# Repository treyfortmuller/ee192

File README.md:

# EE192 Spring 2018: Team 6
Joey Kroeger, Trey Fortmuller, Charlene Shong

### Development Workflow
* The master branch should always be functional.
* For each checkoff, create a branch. When the branch is working and tested, merge it into master.

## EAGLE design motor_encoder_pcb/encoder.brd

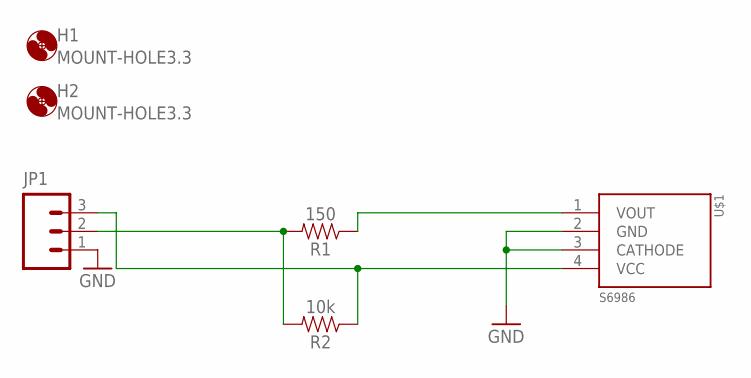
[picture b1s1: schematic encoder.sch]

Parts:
H1, H2: MOUNT-HOLE3.3; 3,3
JP1: M03PTH; 1X03
R1: 150; AXIAL-0.3
R2: 10k; AXIAL-0.3
U$1: S6986

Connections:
GND: JP1.1, U$1.2 (GND), U$1.3 (CATHODE)
unnamed: JP1.2, R1.P$2 (2), R2.P$2 (2)
unnamed: JP1.3, R2.P$1 (1), U$1.4 (VCC)
unnamed: R1.P$1 (1), U$1.1 (VOUT)

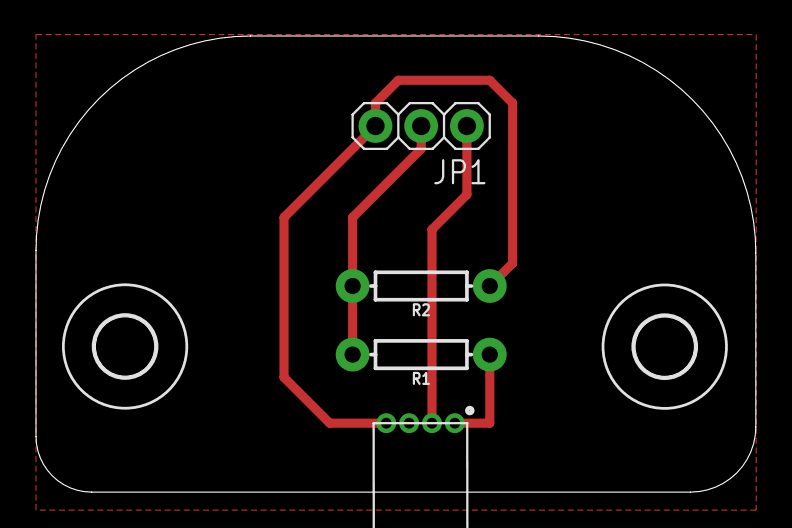
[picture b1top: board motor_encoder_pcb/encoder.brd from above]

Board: 2 copper layers, 40.0 x 25.3 mm, 6 parts (0 on the bottom side), 4 nets.

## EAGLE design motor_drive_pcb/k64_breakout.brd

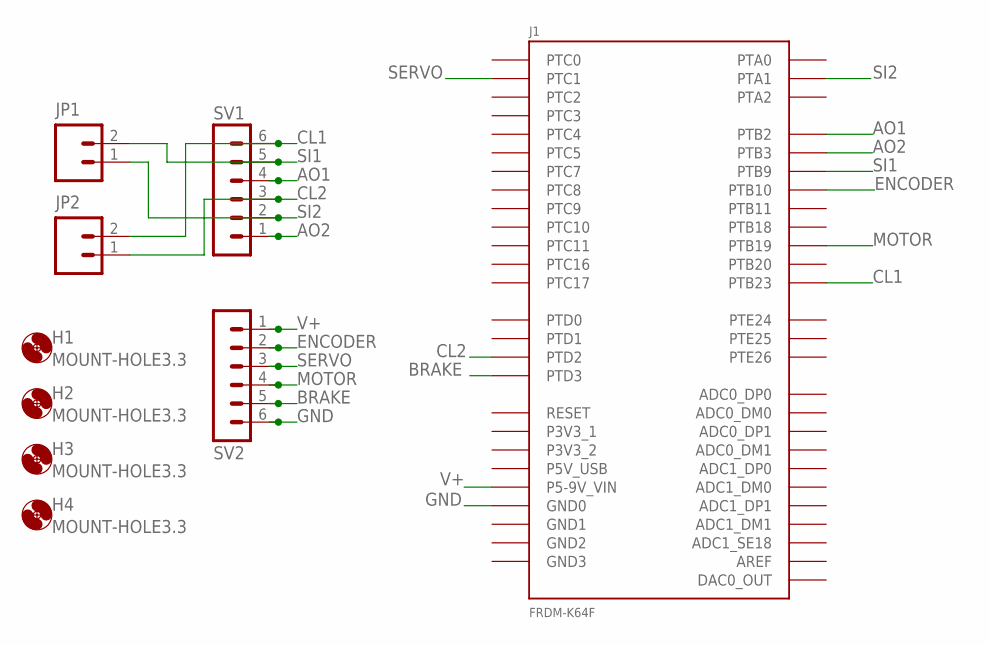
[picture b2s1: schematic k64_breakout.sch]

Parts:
H1, H2, H3, H4: MOUNT-HOLE3.3; 3,3
J1: FRDM-K64F
JP1, JP2: M02PTH; 1X02
SV1, SV2: MA06-1

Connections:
AO1: J1.J4-2 (PTB2), SV1.4
AO2: J1.J4-4 (PTB3), SV1.1
BRAKE: J1.J2-10 (PTD3), SV2.5
CL1: J1.J1-10 (PTB23), JP2.2, SV1.6
CL2: J1.J2-8 (PTD2), JP2.1, SV1.3
ENCODER: J1.J4-6 (PTB10), SV2.2
GND: J1.J2-3 (GND0), SV2.6
MOTOR: J1.J1-3 (PTB19), SV2.4
SERVO: J1.J1-5 (PTC1), SV2.3
SI1: J1.J1-6 (PTB9), JP1.2, SV1.5
SI2: J1.J1-8 (PTA1), JP1.1, SV1.2
V+: J1.J3-16 (P5-9V_VIN), SV2.1

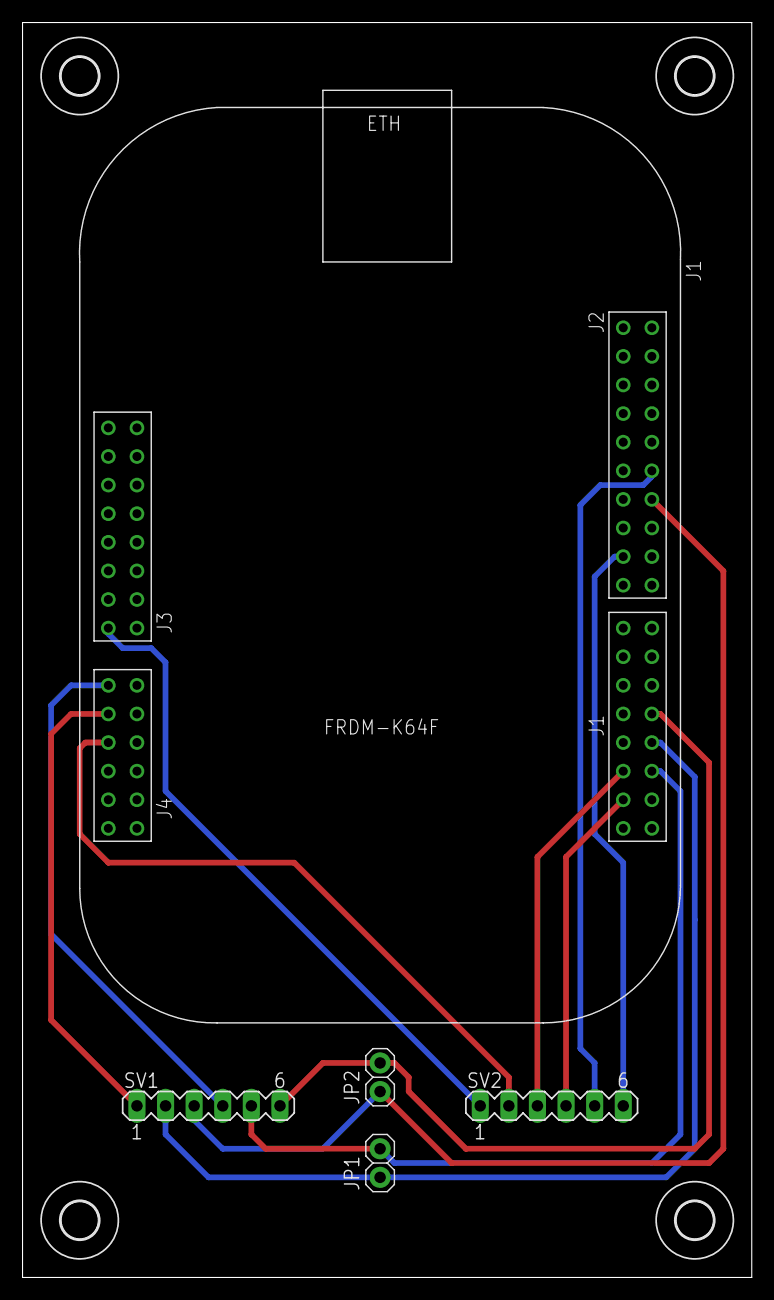
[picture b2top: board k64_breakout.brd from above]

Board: 2 copper layers, 64.8 x 111.4 mm, 9 parts (0 on the bottom side), 12 nets.

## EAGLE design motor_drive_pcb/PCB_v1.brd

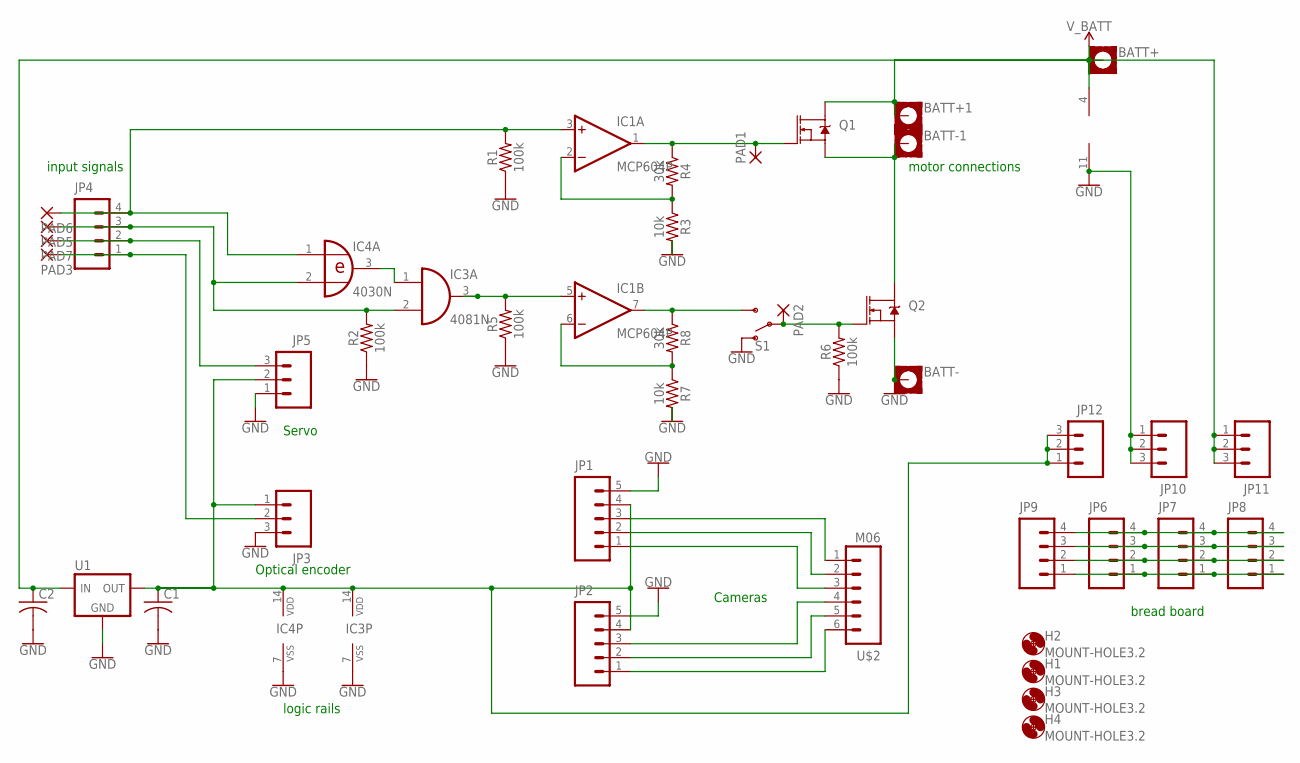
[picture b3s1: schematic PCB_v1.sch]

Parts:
BATT+, BATT+1: MOUNT-PAD-SQUARE3.0; 3,0-PAD-SQUARE
BATT-, BATT-1: MOUNT-PAD-SQUARE3.0; 3,0-PAD-SQUARE
C1, C2: C-075PTH; C075
H1, H2, H3, H4: MOUNT-HOLE3.2; 3,2
IC1: MCP604P; DIL14
IC3: 4081N; DIL14
IC4: 4030N; DIL14
JP1, JP2: M05PTH; 1X05
JP3, JP5, JP10, JP11, JP12: M03PTH; 1X03
JP4, JP6, JP7, JP8, JP9: M04PTH; 1X04
PAD1, PAD2, PAD3, PAD5, PAD6, PAD7: 2,15/1,0
Q1, Q2: MOSFET-NCH-FQP30N06L; TO220V
R1, R2, R5, R6: 100k; AXIAL-0.3
R3, R7: 10k; AXIAL-0.3
R4, R8: 30k; AXIAL-0.3
S1: SWITCH-SPDT-PTH-11.6X4.0MM-KIT; SWITCH_SPDT_PTH_11.6X4.0MM_KIT
U1: 78XX-TO220V; TO220BV
U$2: M06; 1X06-MTA

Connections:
GND: BATT-.B3,0, C1.2 (-), C2.2 (-), IC1.11 (V-), IC3.7 (VSS), IC4.7 (VSS), JP1.5, JP2.5, JP3.3, JP5.1, JP10.1, JP10.2, JP10.3, Q2.3 (S), R1.P$1 (1), R2.P$1 (1), R3.P$2 (2), R5.P$1 (1), R6.P$1 (1), R7.P$2 (2), S1.1 (O), U1.2 (GND)
unnamed: IC1.2 (-IN), R3.P$1 (1), R4.P$2 (2)
unnamed: IC1.1 (OUT), PAD1.1, Q1.1 (G), R4.P$1 (1)
unnamed: IC1.6 (-IN), R7.P$1 (1), R8.P$2 (2)
unnamed: PAD2.1, Q2.1 (G), R6.P$2 (2), S1.2
unnamed: BATT-1.B3,0, Q1.3 (S), Q2.2 (D)
unnamed: IC1.7 (OUT), R8.P$1 (1), S1.3 (S)
unnamed: IC3.1 (I0), IC4.3 (O)
unnamed: JP2.1, U$2.6
unnamed: JP2.2, U$2.5
unnamed: JP2.3, U$2.4
unnamed: JP1.1, U$2.3
unnamed: JP1.2, U$2.2
unnamed: JP1.3, U$2.1
unnamed: JP4.2, JP5.3, PAD7.1
unnamed: IC1.3 (+IN), IC4.1 (I0), JP4.4, PAD6.1, R1.P$2 (2)
unnamed: IC3.2 (I1), IC4.2 (I1), JP4.3, PAD5.1, R2.P$2 (2)
unnamed: C1.1 (+), IC3.14 (VDD), IC4.14 (VDD), JP1.4, JP2.4, JP3.1, JP5.2, JP12.1, JP12.2, JP12.3, U1.3 (VOUT)
unnamed: JP3.2, JP4.1, PAD3.1
unnamed: IC1.5 (+IN), IC3.3 (O), R5.P$2 (2)
unnamed: JP6.4, JP7.4, JP8.4, JP9.4
unnamed: JP6.3, JP7.3, JP8.3, JP9.3
unnamed: JP6.2, JP7.2, JP8.2, JP9.2
unnamed: JP6.1, JP7.1, JP8.1, JP9.1
V_BATT: BATT+.B3,0, BATT+1.B3,0, C2.1 (+), IC1.4 (V+), JP11.1, JP11.2, JP11.3, Q1.2 (D), U1.1 (VIN)

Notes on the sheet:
Optical encoder
Servo
Cameras
input signals
logic rails
motor connections
bread board

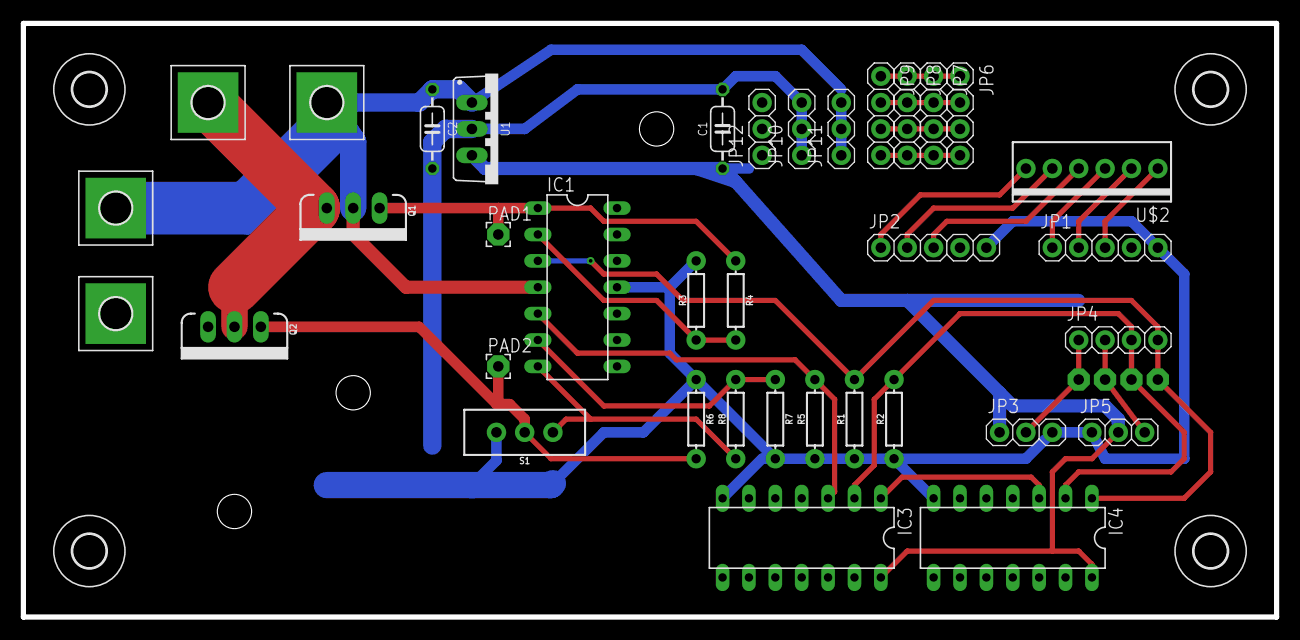
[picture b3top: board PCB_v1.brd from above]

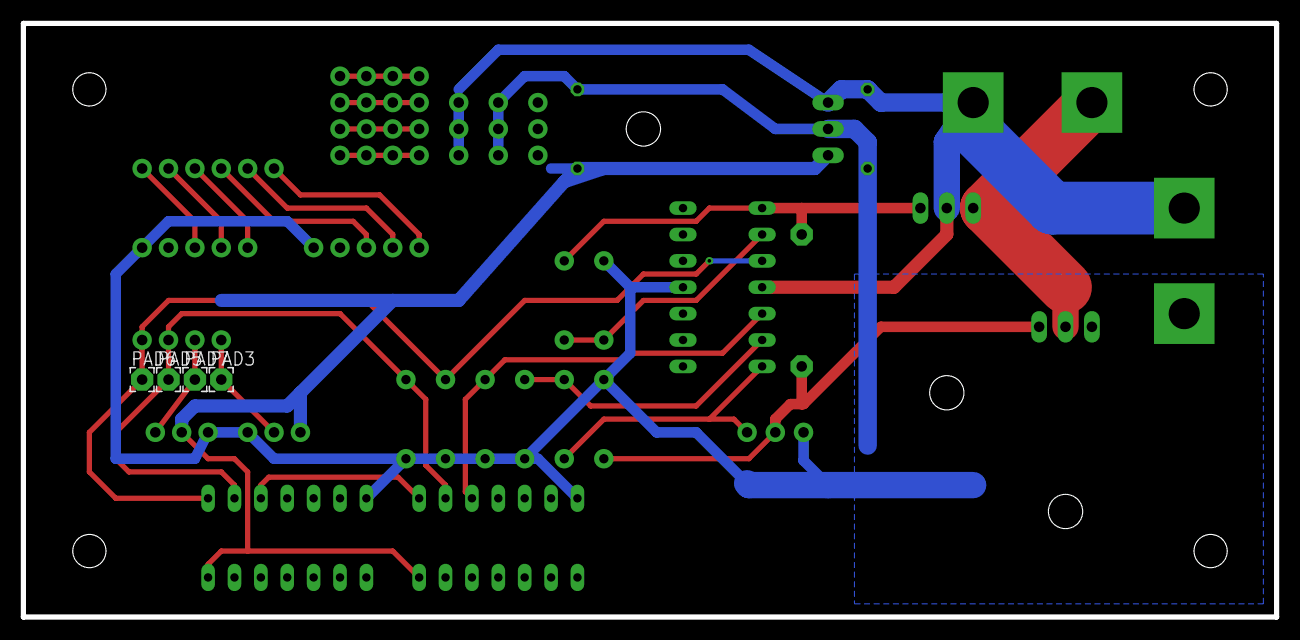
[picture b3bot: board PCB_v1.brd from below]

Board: 2 copper layers, 120.7 x 57.2 mm, 44 parts (4 on the bottom side), 25 nets.

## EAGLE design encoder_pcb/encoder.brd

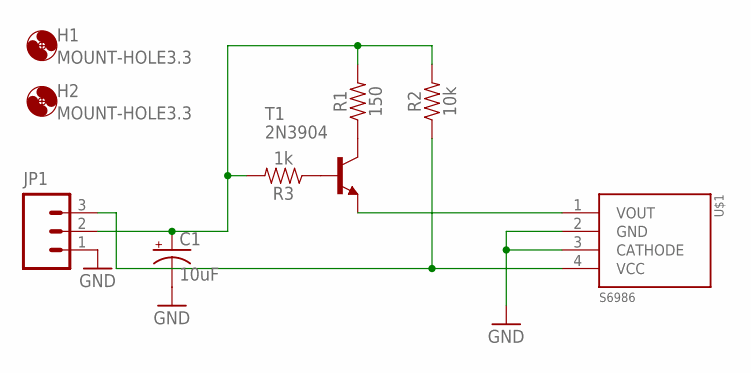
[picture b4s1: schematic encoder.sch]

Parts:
C1: 10uF; CPOL-RADIAL-2.5MM-5MM-KIT
H1, H2: MOUNT-HOLE3.3; 3,3
JP1: M03PTH; 1X03
R1: 150; AXIAL-0.3
R2: 10k; AXIAL-0.3
R3: 1k; AXIAL-0.3
T1: 2N3904; TO92
U$1: S6986

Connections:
GND: C1.2 (-), JP1.1, U$1.2 (GND), U$1.3 (CATHODE)
unnamed: C1.1 (+), JP1.2, R1.P$2 (2), R2.P$2 (2), R3.P$2 (2)
unnamed: JP1.3, R2.P$1 (1), U$1.4 (VCC)
unnamed: R1.P$1 (1), T1.1 (C)
unnamed: R3.P$1 (1), T1.2 (B)
unnamed: T1.3 (E), U$1.1 (VOUT)

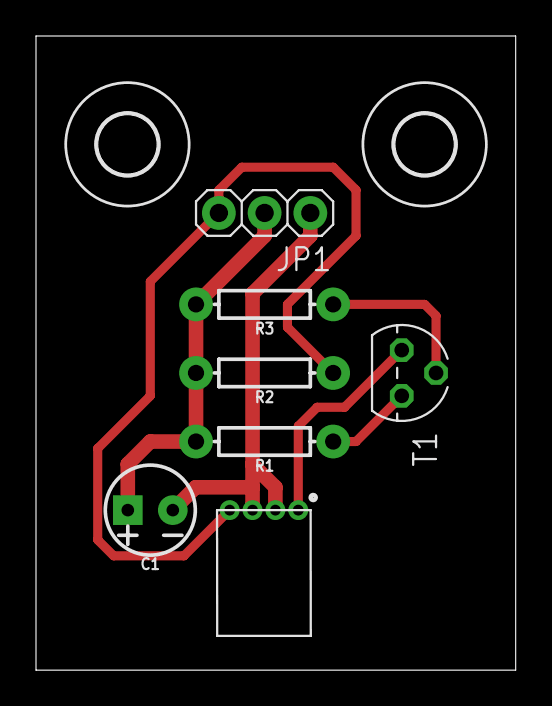
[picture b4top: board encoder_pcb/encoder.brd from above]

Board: 2 copper layers, 26.6 x 35.2 mm, 9 parts (0 on the bottom side), 6 nets.

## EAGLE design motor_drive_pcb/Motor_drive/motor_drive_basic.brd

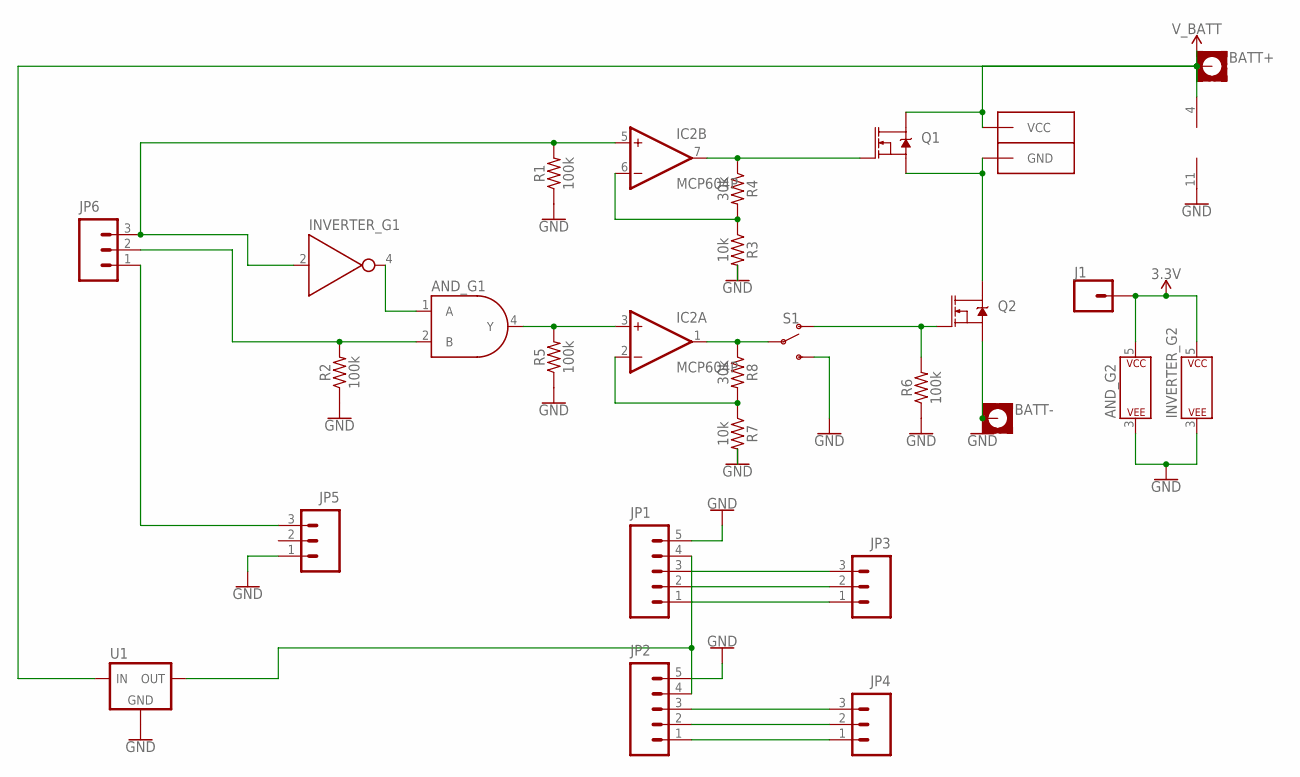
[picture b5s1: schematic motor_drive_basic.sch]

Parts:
AND_: 74LVC08SE; SOT23-5
BATT+: MOUNT-PAD-SQUARE3.0; 3,0-PAD-SQUARE
BATT-: MOUNT-PAD-SQUARE3.0; 3,0-PAD-SQUARE
CONN1: ANDERSON_PP_DOUBLEVERTICAL; ANDERSON_PP_DOUB_VERT
IC2: MCP604P; DIL14
INVERTER_: 74HC1G04; SOT353
J1: CONN_01; 1X01
JP1, JP2: M05PTH; 1X05
JP3, JP4, JP5, JP6: M03PTH; 1X03
Q1, Q2: MOSFET-NCH-FQP30N06L; TO220V
R1, R2, R5, R6: 100k; AXIAL-0.3
R3, R7: 10k; AXIAL-0.3
R4, R8: 30k; AXIAL-0.3
S1: SWITCH-SPDT-PTH-11.6X4.0MM-KIT; SWITCH_SPDT_PTH_11.6X4.0MM_KIT
U1: 78XX-TO220V; TO220BV

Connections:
3.3V: AND_.5 (P$V+), INVERTER_.5 (P$V+), J1.1
GND: AND_.3 (P$V-), BATT-.B3,0, IC2.11 (V-), INVERTER_.3 (P$V-), JP1.5, JP2.5, JP5.1, Q2.3 (S), R1.P$1 (1), R2.P$1 (1), R3.P$2 (2), R5.P$1 (1), R6.P$1 (1), R7.P$2 (2), S1.3 (S), U1.2 (GND)
unnamed: IC2.6 (-IN), R3.P$1 (1), R4.P$2 (2)
unnamed: IC2.7 (OUT), Q1.1 (G), R4.P$1 (1)
unnamed: IC2.2 (-IN), R7.P$1 (1), R8.P$2 (2)
unnamed: AND_.4 (Y), IC2.3 (+IN), R5.P$2 (2)
unnamed: Q2.1 (G), R6.P$2 (2), S1.1 (O)
unnamed: CONN1.PIN1 (GND), Q1.3 (S), Q2.2 (D)
unnamed: IC2.1 (OUT), R8.P$1 (1), S1.2
unnamed: AND_.1 (A), INVERTER_.4 (Y)
unnamed: JP2.1, JP4.1
unnamed: JP2.2, JP4.2
unnamed: JP2.3, JP4.3
unnamed: JP1.1, JP3.1
unnamed: JP1.2, JP3.2
unnamed: JP1.3, JP3.3
unnamed: JP5.3, JP6.1
unnamed: IC2.5 (+IN), INVERTER_.2 (A), JP6.3, R1.P$2 (2)
unnamed: AND_.2 (B), JP6.2, R2.P$2 (2)
unnamed: JP1.4, JP2.4, U1.3 (VOUT)
V_BATT: BATT+.B3,0, CONN1.PIN2 (VCC), IC2.4 (V+), Q1.2 (D), U1.1 (VIN)

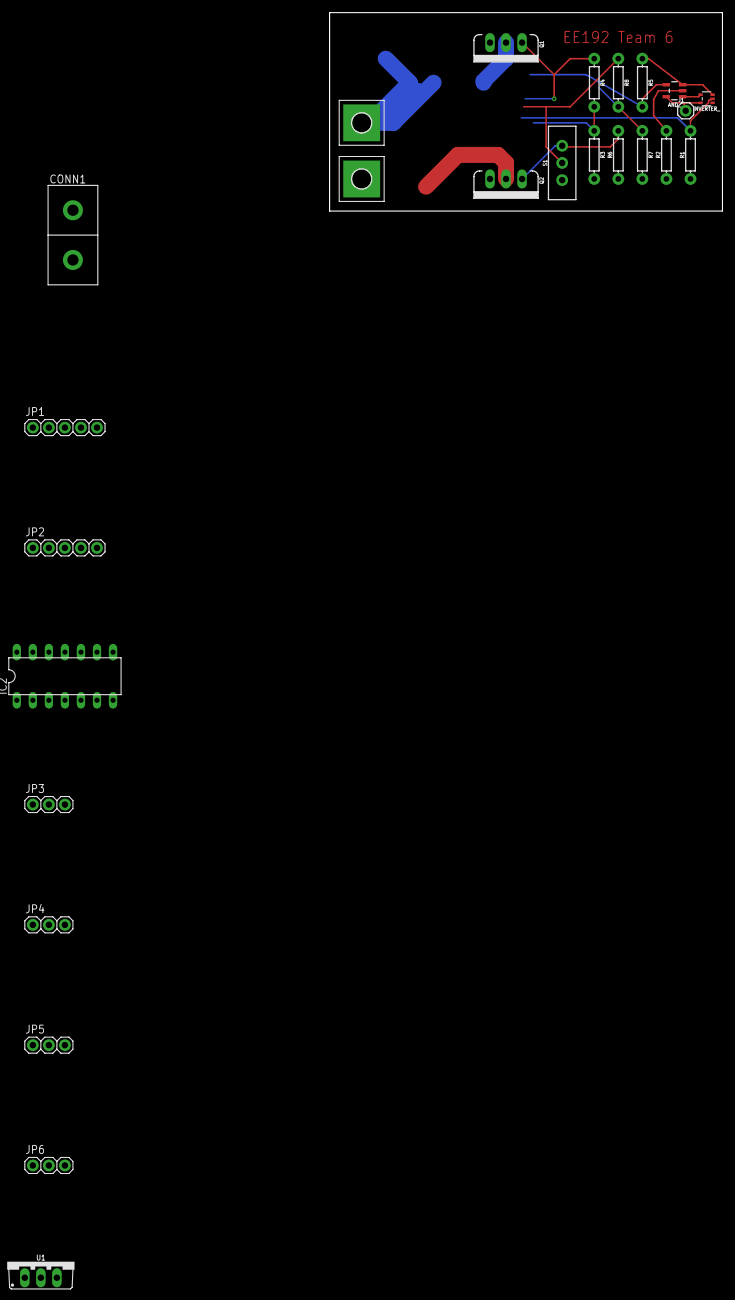
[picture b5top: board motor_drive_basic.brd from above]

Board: 2 copper layers, 62.2 x 31.4 mm, 25 parts (0 on the bottom side), 21 nets.

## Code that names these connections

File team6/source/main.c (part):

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 * PTD3 - FTM3 - Braking PWM?
 * PTA1 - GPIOA - SI for LSC2
 * PTD2 - GPIOD - CLK for LCS2
 * PTC16 - GPIOC - Encoder Timing?
 */

/* The Flex Timer Module (FTM) instance/channel used for board. See pin view or open declaration for more info */
#define BOARD_FTM_BASEADDR_SERVO FTM0
#define BOARD_FTM_BASEADDR_MOTOR FTM2
#define BOARD_FTM_CHANNEL_SERVO kFTM_Chnl_0 // pin PTC1, servo PWM
#define BOARD_FTM_CHANNEL_MOTOR kFTM_Chnl_1 // pin PTB19, motor PWM

/* Interrupt to enable and flag to read; depends on the FTM channel used */
#define FTM_CHANNEL_INTERRUPT_ENABLE_SERVO kFTM_Chnl0InterruptEnable // servo
#define FTM_CHANNEL_FLAG_SERVO kFTM_Chnl0Flag

#define FTM_CHANNEL_INTERRUPT_ENABLE_MOTOR kFTM_Chnl1InterruptEnable // motor
#define FTM_CHANNEL_FLAG_MOTOR kFTM_Chnl1Flag

/* Get source clock for FTM driver */
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 *
 */
/* Get source clock for FTM driver, we're looking for ~400Hz PWM for the motor */
#define FTM_SOURCE_CLOCK_SERVO CLOCK_GetFreq(kCLOCK_BusClk) // servo (slow PWM)
#define FTM_SOURCE_CLOCK_MOTOR CLOCK_GetFreq(kCLOCK_BusClk) // motor (high PWM)

// High Voltage(3.3V)=True for PWM
#define PWM_LEVEL kFTM_HighTrue
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
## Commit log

2018-01-24 updated readme again
2018-01-24 adjusted readme again
2018-01-26 Add files via upload
    added blink_led files with changes from office hours; should now work for checkoff
2018-01-26 test
2018-01-26 remove test text file
2018-01-26 reorganized the repo
2018-01-26 deleted the file you uploaded rather than pushed
    push and pull after committing changes to git, don't upload files, they aren't tracked.
2018-01-26 clean up code, added comments, added skeleton code so the project can be built
2018-01-26 switched supporting files for checkoff_1 to blink_led skeleton
2018-01-29 motor drive circuit schematic
2018-02-05 research notes
2018-02-08 added steering servo pwm output logic
2018-02-08 ignore
2018-02-09 removed webloc for charlene
2018-02-09 checkoff 3
2018-02-16 successful code for checkoff 3
2018-02-19 created a readme again?
2018-02-21 eagle schematic
2018-02-21 added datasheets
2018-02-21 PCB updates
2018-02-28 added the k64 pinout picture
2018-03-01 readme updates, setup guide, checkoff 5 started
2018-03-01 updates to PCB
2018-03-01 moved adc demo code into main.c
2018-03-01 tcrt optical encoder datasheet and info
2018-03-01 checkoff 5 changes
2018-03-02 velocity sensing logic
2018-03-02 updated main/c for velocity sensing
2018-03-03 checkoff 5 attempt
2018-03-07 hw1 files and directory
2018-03-07 reorganization and new working project directory
2018-03-07 working project from now on
2018-03-07 directory clean up
2018-03-07 some new datasheets
2018-03-07 removed unneccessary debug launchers
2018-03-07 removed an extraneous .project
2018-03-08 added mosfet datasheet
2018-03-08 branch issues
2018-03-09 added console based telemetry output for line tracking
2018-03-09 working checkoff6
2018-03-12 changes to main for second FTM0 channel and pin
2018-03-13 working plotting code for hw1
2018-03-13 working plots
2018-03-13 individual frame plotting
2018-03-13 working line detecting algorithm, crosses still problematic
2018-03-13 completed hw1
2018-03-16 changes to main for servo commands for figure 8
2018-03-20 working checkoff7 code
2018-03-20 working camera and new pwm pin
2018-03-21 second adc pin PTB10 initialization code added
2018-03-23 both adc pins working but linear encoder not reading
2018-03-23 complete hw2 files
2018-03-23 included the hw2 pdf for submission
2018-04-02 new pins initialized
2018-04-03 new sim model
2018-04-05 encoder PCB started
2018-04-05 added the encoder PCB desing files
2018-04-05 updated pcb and encoder schematics and boards
2018-04-05 encoder pcb changes
2018-04-05 pcb outputs
2018-04-06 telemetry skeleton code
2018-04-06 line_algo improvements
2018-04-06 added client side telemtry from Varun
2018-04-06 moved client side telemetry scripts to the root directory
2018-04-06 added telemetry code but not functional
2018-04-06 linescan algo improvements
2018-04-06 ignore, not working
2018-04-06 some additional line tracking and functioning path following code
2018-04-06 some small potential fixes
2018-04-06 ignore, bad
2018-04-06 working code from checkoff7
2018-04-06 exposure control logic psuedocode
2018-04-06 not working telemetry code
2018-04-06 working checkoff9 code 70s w/o telemetry
2018-04-07 correctly restructured but nonfunctional code w/ telemetry
2018-04-07 new encoder PCB output
2018-04-08 fixed encoder board to have proper spacing of encoder mounting holes for othermill
2018-04-09 sort of working velocity command based on servo pwm
2018-04-22 working adjusted checkoff7 code for lower freq for servos
2018-04-22 cleaned-up but non-functional code
2018-04-23 working code with PIT timing and velocity control
2018-04-23 barely working code with new servo and new motor
2018-04-23 working code for old motor and servo
2018-04-23 ACTUAL WORKING CODE W/ 55 SEC LAPS
2018-04-23 final-ish code for race 2

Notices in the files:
parts and their libraries:
SparkFun-Resistors: Licensing: Creative Commons ShareAlike 4.0 International - https://creativecommons.org/licenses/by-sa/4.0
